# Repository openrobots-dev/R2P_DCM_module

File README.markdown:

MOTORBOARD MODULE
-----------------

This is a motor controller board that features an high power 24V, 20A H-bridge, current sense and quadrature encoder interface.
The MotorBoard module is supposed to work together with other smart modules, publishing data on CAN bus using a publish/subscriber QoS enabled middleware (under development).
The overall system should provide the devices and functionalities commonly used in robot prototyping, speeding up the development process and reducing the engineering time, leaving more time to research activities. The system is also supposed to enable students and amateurs to easily build robots without advanced hardware knowledge.

### Hardware

The MotorBoard module is run by a STM32 ARM Cortex-M3 microcontroller that generates driving signals for the H-Bridge, monitors the current drawn by the motor and reads the incremental encoder feedback.
The microcontroller also runs a PID controller that can follow a position, speed or current (torque) set-point received on a specific topic over the CAN bus network.

The power stage of the MotorBoard features:

- ST STD120N4F6 N-channel 40 V, 3.5 mOhm, 80A power MOSFETs
- Allegro A4941 MOSFET driver
- Allegro ACS711 Hall-effect current sensor

Modules are connected together by a single cable, that transports CAN signals and 5V power. Each module has two ports, enabling chain connections.

A double connector footprint (RJ45 + pin header) is provided, so the user can choose which cabling fits better his needs:

- RJ45 has been chosen as it provides shielded twisted wires for 1Mbit CAN networking in harsh environments and cables are easy to find.
- pin header has been chosen to also give a space saving and simple connection when modules are close and RJ45 jack/plug pairing space is a problem. This header also enables using the IMU module outside our framework, accessing it through a simple TTL UART interface.

The four status LEDs are placed under RJ45 plug light pipes entrance, so it is only needed to solder the preferred connector without any other layout changes.

The left connector has the option to expose the TTL UART interface, instead of the CAN bus interface, by a solder jumper placed on the bottom of the board.

### Firmware

A demo firmware which tests the various hardware components is available.
The full firmware featuring closed loop control is under development.

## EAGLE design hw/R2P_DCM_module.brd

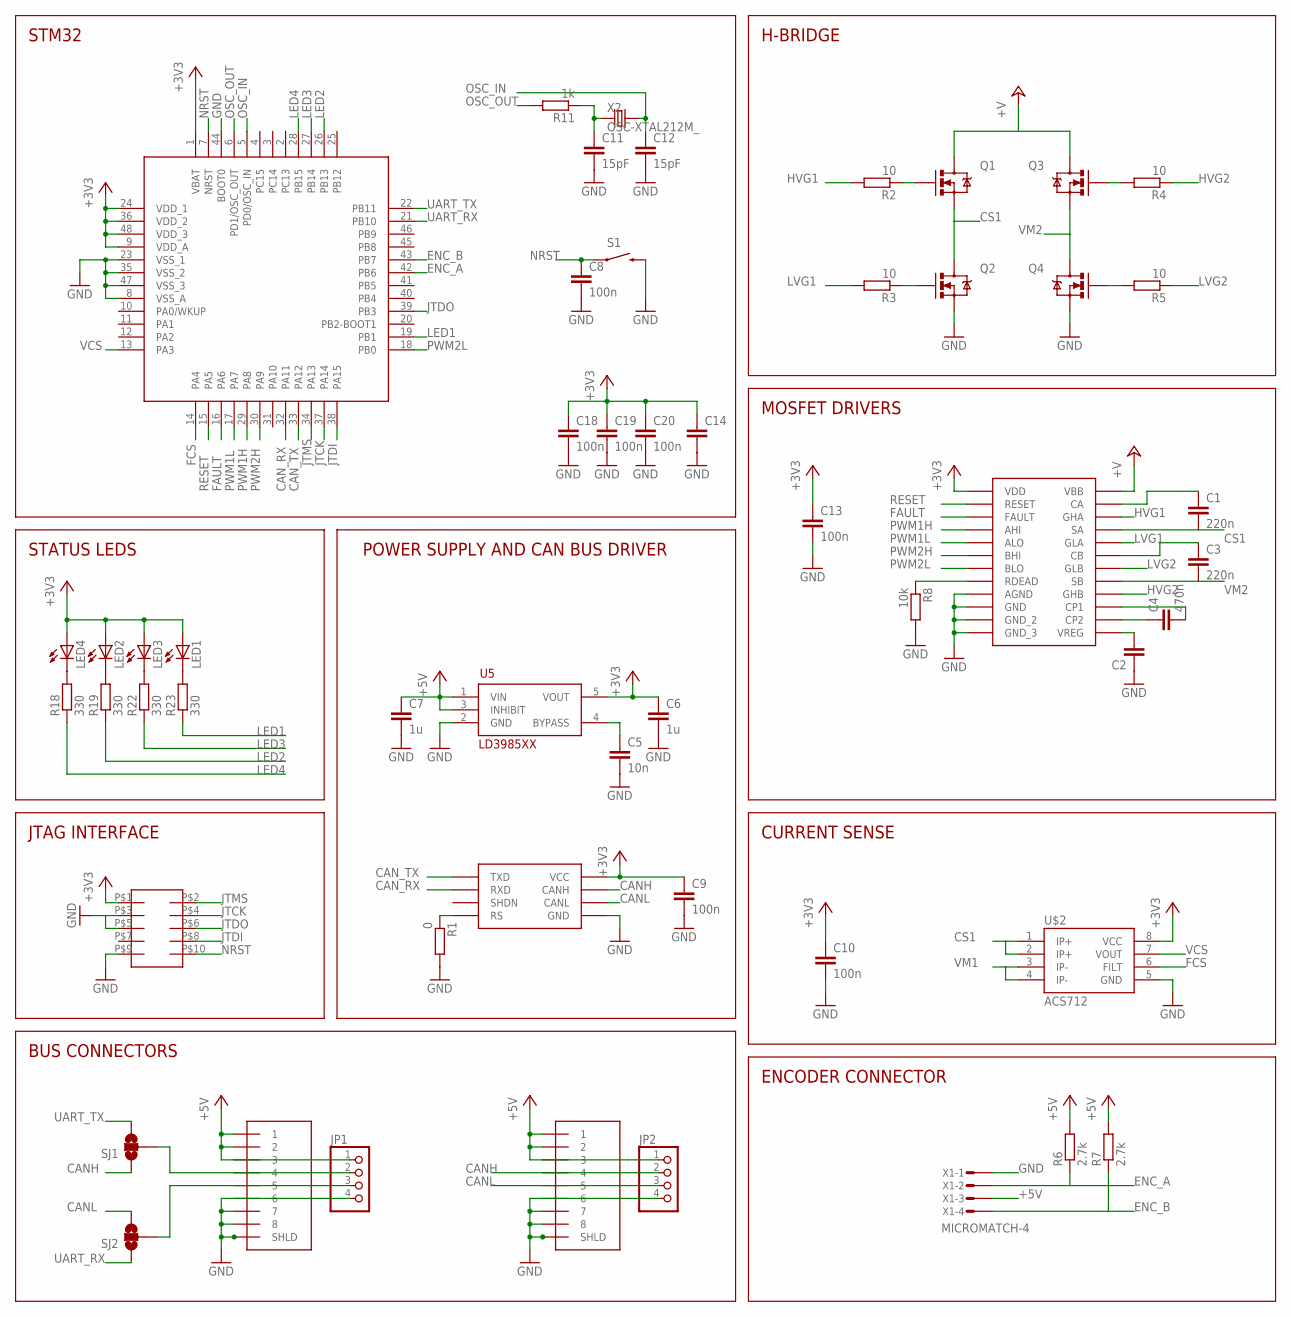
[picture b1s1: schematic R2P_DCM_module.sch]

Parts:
1, 2: RJ45-43860; 0438600010
C1, C3: 220n; C0603
C2, C14: C-EUC0805; C0805
C4: 470n; C0603
C5: 10n; C0603
C6, C7: 1u; C0603
C8, C9, C10, C13, C18, C19, C20: 100n; C0603
C11, C12: 15pF; C0603
JP1, JP2: PINHD-1X4/90; 1X04/90
LED1, LED2, LED3, LED4: LEDCHIPLED_0805; CHIPLED_0805
Q1, Q2, Q3, Q4: MOSFET-NCHANNELFDD8580; DPAK
R1: 0; R0603
R2, R3, R4, R5: 10; R0603
R6, R7: 2.7k; R0603
R8: 10k; R0603
R11: 1k; R0603
R18, R19, R22, R23: 330; R0603
S1: SWITCH-MOMENTARY-2-SMD-1101NE; TACTILE-SWITCH-1101NE
SJ1, SJ2: SOLDERJUMPER_2WAYPASTE1&2; SJ_3_PASTE1&2
SOT1: MAX3051; SOT23-8L
U1: STM32F103CX; LQFP48
U5: LD3985XX; SOT23-5L
U$1: A4940; TSSOP24
U$2: ACS712; SO08
U$4: FTSH-105
X1: MICROMATCH-4
X2: OSC-XTAL212M_; 4X6

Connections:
+3V3: C6.1, C9.1, C10.1, C13.1, C14.1, C18.1, C19.1, C20.1, LED1.A, LED2.A, LED3.A, LED4.A, SOT1.P$3 (VCC), U1.1 (VBAT), U1.9 (VDD_A), U1.24 (VDD_1), U1.36 (VDD_2), U1.48 (VDD_3), U5.5 (VOUT), U$1.21 (VDD), U$2.8 (VCC), U$4.P$1
+5V: 1.P$1 (1), 1.P$2 (2), 1.P$3 (3), 2.P$1 (1), 2.P$2 (2), 2.P$3 (3), C7.1, JP1.1, JP2.1, R6.2, R7.2, U5.1 (VIN), U5.3 (INHIBIT), X1.3
+V: Q1.4 (D), Q3.4 (D), U$1.12 (VBB)
CANH: 2.P$4 (4), JP2.2, SJ1.1, SOT1.P$7 (CANH)
CANL: 2.P$5 (5), JP2.3, SJ2.3, SOT1.P$6 (CANL)
CAN_RX: SOT1.P$4 (RXD), U1.32 (PA11)
CAN_TX: SOT1.P$1 (TXD), U1.33 (PA12)
CS1: C1.2, Q1.3 (S), Q2.4 (D), U$1.10 (SA), U$2.1 (IP+), U$2.2 (IP+)
ENC_A: R6.1, U1.42 (PB6), X1.2
ENC_B: R7.1, U1.43 (PB7), X1.4
FAULT: U1.16 (PA6), U$1.24 (FAULT)
FCS: U1.14 (PA4), U$2.6 (FILT)
GND: 1.P$6 (6), 1.P$7 (7), 1.P$8 (8), 1.P$9 (SHLD), 1.P$10, 2.P$6 (6), 2.P$7 (7), 2.P$8 (8), 2.P$9 (SHLD), 2.P$10, C2.1, C5.2, C6.2, C7.2, C8.2, C9.2, C10.2, C11.2, C12.2, C13.2, C14.2, C18.2, C19.2, C20.2, JP1.4, JP2.4, Q2.3 (S), Q4.3 (S), R1.2, R8.2, S1.P$2 (2), SOT1.P$2 (GND), U1.8 (VSS_A), U1.23 (VSS_1), U1.35 (VSS_2), U1.44 (BOOT0), U1.47 (VSS_3), U5.2 (GND), U$1.2 (GND), U$1.15 (GND_2), U$1.16 (GND_3), U$1.22 (AGND), U$1.PAD (GND), U$2.5 (GND), U$4.P$3, U$4.P$9, X1.1
HVG1: R2.2, U$1.9 (GHA)
HVG2: R4.1, U$1.5 (GHB)
JTCK: U1.37 (PA14), U$4.P$4
JTDI: U1.38 (PA15), U$4.P$8
JTDO: U1.39 (PB3), U$4.P$6
JTMS: U1.34 (PA13), U$4.P$2
LED1: R23.1, U1.19 (PB1)
LED2: R19.1, U1.26 (PB13)
LED3: R22.1, U1.27 (PB14)
LED4: R18.1, U1.28 (PB15)
LVG1: R3.2, U$1.11 (GLA)
LVG2: R5.1, U$1.3 (GLB)
unnamed: R1.1, SOT1.P$8 (RS)
unnamed: 1.P$4 (4), JP1.2, SJ1.2
unnamed: C5.1, U5.4 (BYPASS)
unnamed: Q1.1 (G), R2.1
unnamed: Q2.1 (G), R3.1
unnamed: Q3.1 (G), R4.2
unnamed: 1.P$5 (5), JP1.3, SJ2.2
unnamed: Q4.1 (G), R5.2
unnamed: C4.1, U$1.13 (CP2)
unnamed: C4.2, U$1.14 (CP1)
unnamed: C11.1, R11.1, X2.1 (X1)
unnamed: C2.2, U$1.7 (VREG)
unnamed: LED4.C, R18.2
unnamed: C3.1, U$1.6 (CB)
unnamed: R8.1, U$1.23 (RDEAD)
unnamed: LED2.C, R19.2
unnamed: LED3.C, R22.2
unnamed: LED1.C, R23.2
unnamed: C1.1, U$1.8 (CA)
NRST: C8.1, S1.P$1 (1), U1.7 (NRST), U$4.P$10
OSC_IN: C12.1, U1.5 (PD0/OSC_IN), X2.2 (X2)
OSC_OUT: R11.2, U1.6 (PD1/OSC_OUT)
PWM1H: U1.29 (PA8), U$1.20 (AHI)
PWM1L: U1.17 (PA7), U$1.19 (ALO)
PWM2H: U1.30 (PA9), U$1.18 (BHI)
PWM2L: U1.18 (PB0), U$1.17 (BLO)
RESET: U1.15 (PA5), U$1.1 (RESET)
UART_RX: SJ2.1, U1.21 (PB10)
UART_TX: SJ1.3, U1.22 (PB11)
VCS: U1.13 (PA3), U$2.7 (VOUT)
VM1: U$2.3 (IP-), U$2.4 (IP-)
VM2: C3.2, Q3.3 (S), Q4.4 (D), U$1.4 (SB)

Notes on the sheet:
STM32
POWER SUPPLY AND CAN BUS DRIVER
STATUS LEDS
JTAG INTERFACE
BUS CONNECTORS
H-BRIDGE
MOSFET DRIVERS
CURRENT SENSE
ENCODER CONNECTOR

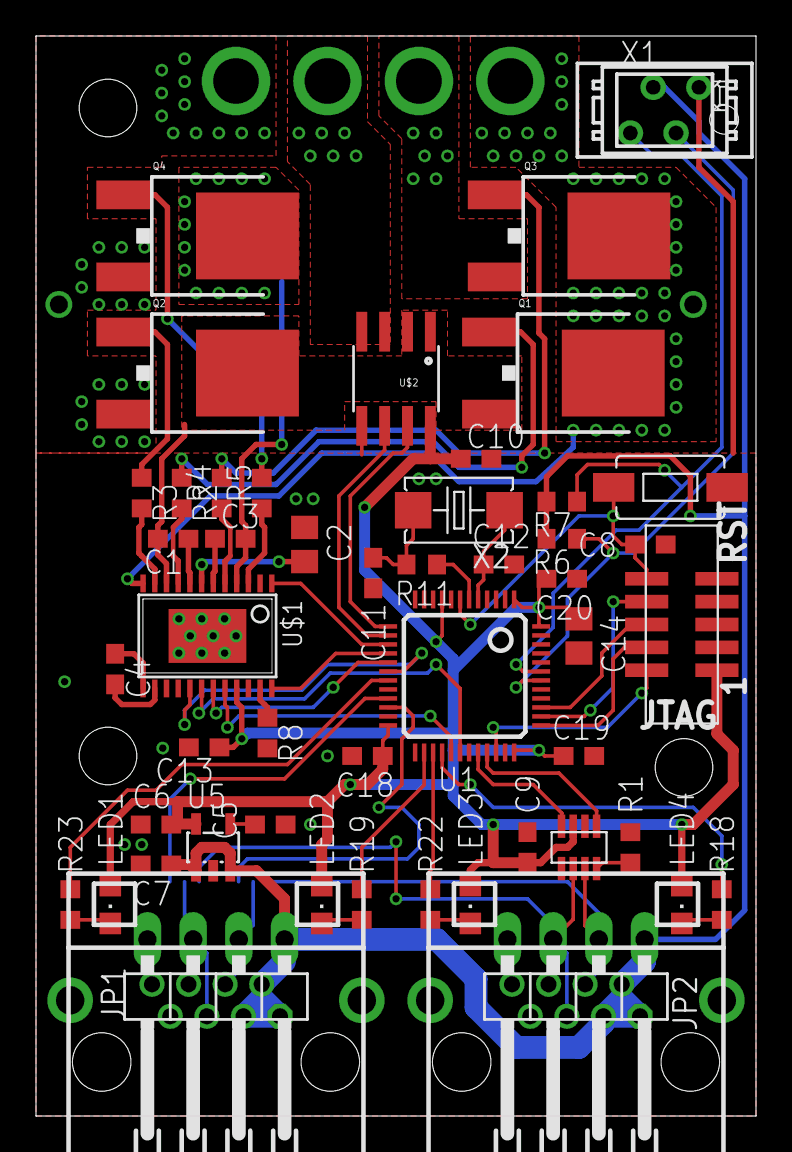
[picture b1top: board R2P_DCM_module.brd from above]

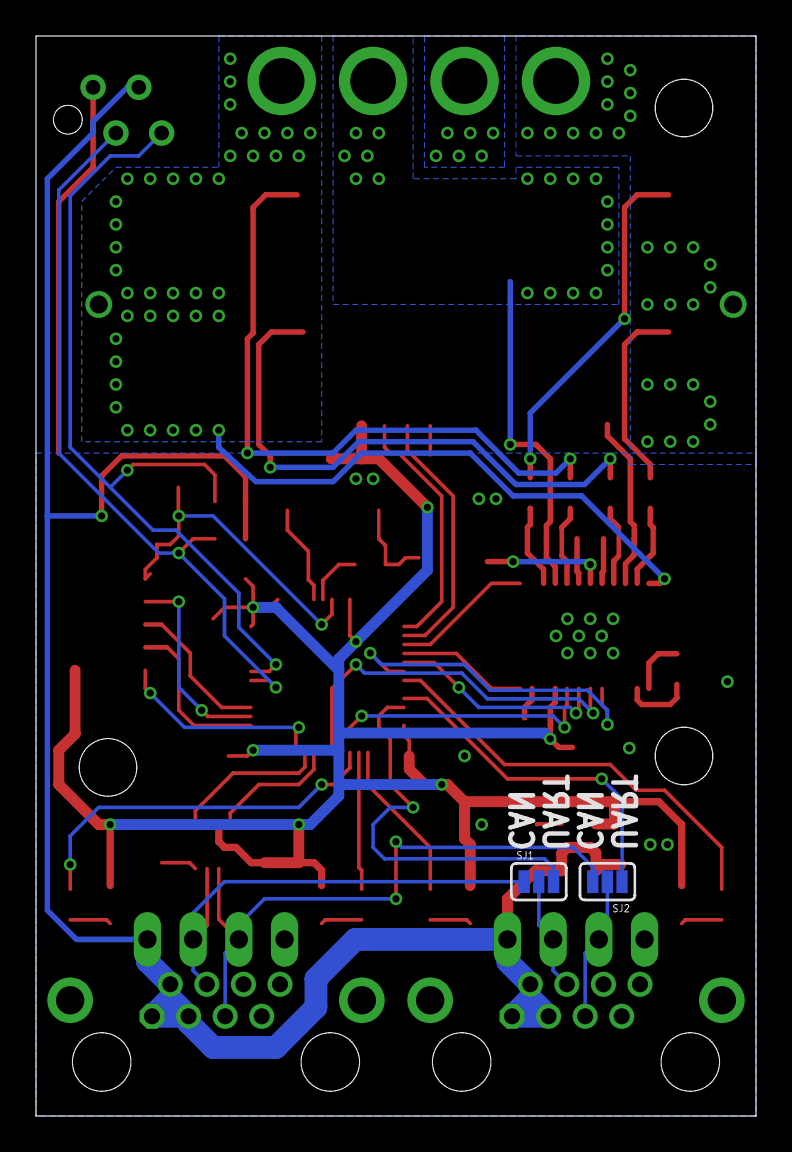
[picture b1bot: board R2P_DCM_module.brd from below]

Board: 2 copper layers, 40.0 x 60.0 mm, 53 parts (2 on the bottom side), 57 nets.

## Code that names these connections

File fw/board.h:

/*
 ChibiOS/RT - Copyright (C) 2006,2007,2008,2009,2010,
 2011 Giovanni Di Sirio.

 This file is part of ChibiOS/RT.

 ChibiOS/RT is free software; you can redistribute it and/or modify
 it under the terms of the GNU General Public License as published by
 the Free Software Foundation; either version 3 of the License, or
 (at your option) any later version.

 ChibiOS/RT is distributed in the hope that it will be useful,
 but WITHOUT ANY WARRANTY; without even the implied warranty of
 MERCHANTABILITY or FITNESS FOR A PARTICULAR PURPOSE.  See the
 GNU General Public License for more details.

 You should have received a copy of the GNU General Public License
 along with this program.  If not, see <http://www.gnu.org/licenses/>.
 */

#ifndef _BOARD_H_
#define _BOARD_H_

/*
 * Setup for the R2P DC motor module.
 */

/*
 * Board identifier.
 */
#define BOARD_R2P_DCM_MODULE
#define BOARD_NAME              "R2P DC motor module"

/*
 * Board frequencies.
 */
#define STM32_LSECLK            32768
#define STM32_HSECLK            8000000

/*
 * MCU type, supported types are defined in ./os/hal/platforms/hal_lld.h.
 */
#define STM32F10X_MD
#define STM32F10X


/*
 * IO pins assignments.
 */
#define LED1_GPIO				GPIOB
#define LED1					1
#define LED2_GPIO				GPIOB
#define LED2					13
#define LED3_GPIO				GPIOB
#define LED3					14
#define LED4_GPIO				GPIOB
#define LED4					15

#define DRIVER_GPIO             GPIOA
#define DRIVER_RESET            5
#define DRIVER_FAULT            6

#define SERIAL_DRIVER           SD3
//#define SERIAL_DRIVER           SD1

#define PWM_DRIVER              PWMD1
#define QEI_DRIVER              QEID4

/*
 * I/O ports initial setup, this configuration is established soon after reset
 * in the initialization code.
 *
 * The digits have the following meaning:
 *   0 - Analog input.
 *   1 - Push Pull output 10MHz.
 *   2 - Push Pull output 2MHz.
 *   3 - Push Pull output 50MHz.
 *   4 - Digital input.
 *   5 - Open Drain output 10MHz.
 *   6 - Open Drain output 2MHz.
 *   7 - Open Drain output 50MHz.
 *   8 - Digital input with PullUp or PullDown resistor depending on ODR.
 *   9 - Alternate Push Pull output 10MHz.
 *   A - Alternate Push Pull output 2MHz.
 *   B - Alternate Push Pull output 50MHz.
 *   C - Reserved.
 *   D - Alternate Open Drain output 10MHz.
 *   E - Alternate Open Drain output 2MHz.
 *   F - Alternate Open Drain output 50MHz.
 * Please refer to the STM32 Reference Manual for details.
 */

/*
 * Port A setup.
 * Everything input with pull-up except:
 * PA3  - Analog input     (CS_OUT).
 * PA4  - Input with PU    (CS_FAULT).
 * PA5  - Push Pull output (DRIVER_RESET).
 * PA6  - Input with PU    (DRIVER_FAULT).
 * PA7  - Alternate output (PWM1L).
 * PA8  - Alternate output (PWM1H).
 * PA9  - Alternate output (PWM2H).
 * PA11 - Normal input     (CAN1 RX).
 * PA12 - Alternate output (CAN1 TX).
 */
#define VAL_GPIOACRL            0xB8380888      /*  PA7...PA0 */
#define VAL_GPIOACRH            0x888B48BB      /* PA15...PA8 */
#define VAL_GPIOAODR            0xFFFFFFFF

/*
 * Port B setup.
 * Everything input with pull-up except:
 *
 * PB0  - Alternate output (PWM2L).
 * PB1  - Push Pull output (LED1).
 * PB6  - Normal input (ENC_A).
 * PB7  - Normal input (ENC_B).
 * PB10 - Alternate output (USART3 TX).
 * PB11 - Normal input     (USART3 RX).
 * PB13 - Push Pull output (LED2).
 * PB14 - Push Pull output (LED3).
 * PB15 - Push Pull output (LED4).
 */
#define VAL_GPIOBCRL            0x4488883B      /*  PB7...PB0 */
//#define VAL_GPIOBCRL            0x4B88883B      /*  XXX USART1 REMAP */
#define VAL_GPIOBCRH            0x33384BFF      /* PB15...PB8 */
#define VAL_GPIOBODR            0xFFFFFFFF

/*
 * Port C setup.
 * Everything input with pull-up except:
 */
#define VAL_GPIOCCRL            0x88888888      /*  PC7...PC0 */
#define VAL_GPIOCCRH            0x88888888      /* PC15...PC8 */
#define VAL_GPIOCODR            0xFFFFFFFF

#if !defined(_FROM_ASM_)
#ifdef __cplusplus
extern "C" {
#endif
void boardInit(void);
#ifdef __cplusplus
}
#endif
#endif /* _FROM_ASM_ */

#endif /* _BOARD_H_ */

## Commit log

2011-09-16 fixed PNG link
2011-09-27 Edited README.markdown via GitHub
2012-07-24 Removed signals under A4940
2012-07-24 Typo in schematics and board layout filename
2012-07-24 Powerpad under A4940
2012-07-30 Datasheets added
2012-07-30 .gitignore added to revision control
2012-08-28 Update MCU layout
2012-09-27 Test firmware commit
2012-10-15 Added test main files
2012-10-15 Added eclipse project files and launch configuration
2012-10-16 Added encoder interface
2012-10-17 Added board .png
2012-10-17 Fixed .png url
2012-10-17 Updated board.png
2012-10-18 Created control branch
2012-10-18 Removed launch configuration
2012-11-22 Removed misplaced via and disconnected MAX3051 shutdown pin
2013-02-21 Added R2P middleware test
2013-02-21 custom linker script
2013-05-09 Speed and Pidsetup from R2P messages
2013-08-01 increased bootstrap capacitor value
2013-08-01 Corrected RDEAD value
2013-09-25 ported to mw v2
2013-09-29 shared nodes
2013-11-27 small fixes
2013-12-16 fixed makefile
2013-12-16 added missing files
2013-12-16 added missing launch file
2014-02-12 up to date
2014-03-06 dcm ok
2014-03-07 removed unused defines
2014-03-07 updated sample firmware to mw v2
2014-03-14 bugfix
2014-03-14 usad firmware ready
2014-03-18 fixed encoder resolution
2014-03-19 tuned steer PID
2014-04-23 demo working
2014-04-23 just a test commit
2014-04-23 just another test commit
2014-04-23 added QEI driver sources
2014-06-23 removed duplicated via
2014-07-09 moved led blink to board init
2014-07-28 restored blinking led demo
2014-07-29 working on demo
2014-10-20 added odometry
